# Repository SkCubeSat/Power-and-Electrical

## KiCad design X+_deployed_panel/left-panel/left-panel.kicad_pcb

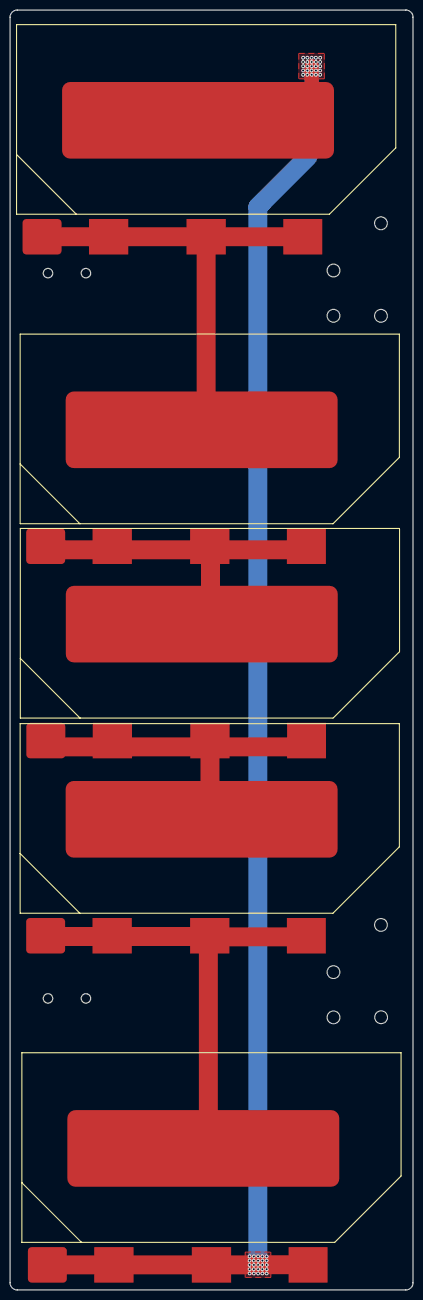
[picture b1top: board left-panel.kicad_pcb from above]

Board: 2 copper layers, 85.0 x 270.0 mm, 14 parts (1 on the bottom side), 6 nets.

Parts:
Buck1: DF13_Horizontal
H1, H4, H5, H6, H7, H8, H9, H10: MountingHole; MountingHole_2.7mm_M2.5
SC1, SC3, SC4, SC5, SC6: S8040_CIC; Solar_Cell_Lightricity_S8040_CIC

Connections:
unnamed: Buck1.1 (BCR+), SC6.2 (-)
unnamed: Buck1.2 (BCR-), SC1.1 (+)
unnamed: SC1.2 (-), SC3.1 (+)
unnamed: SC3.2 (-), SC4.1 (+)
unnamed: SC4.2 (-), SC5.1 (+)
unnamed: SC5.2 (-), SC6.1 (+)

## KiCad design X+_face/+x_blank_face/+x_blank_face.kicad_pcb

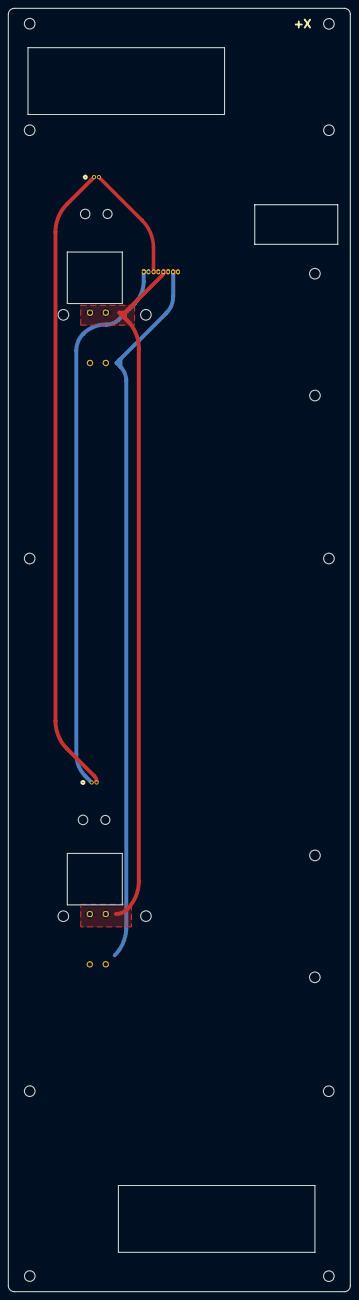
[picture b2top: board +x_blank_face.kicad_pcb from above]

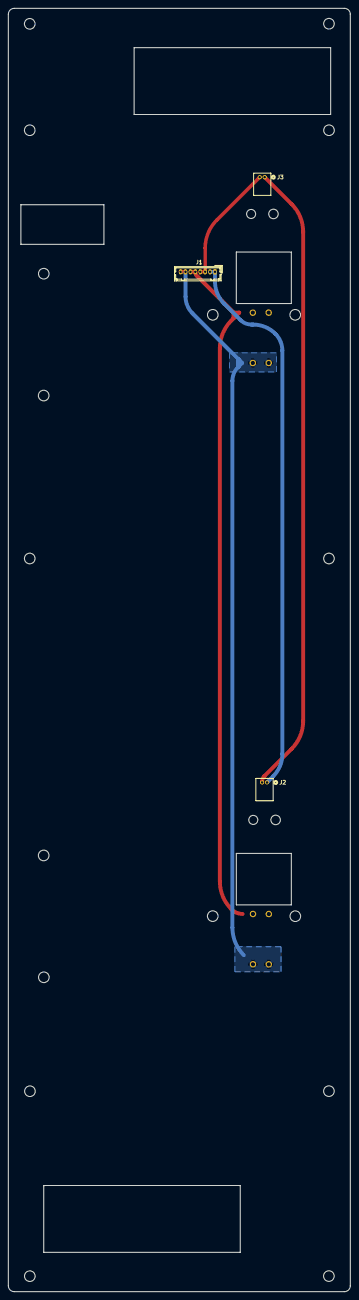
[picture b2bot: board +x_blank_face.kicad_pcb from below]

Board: 2 copper layers, 87.0 x 326.5 mm, 25 parts (3 on the bottom side), 5 nets.

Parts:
H1, H1#2, H2, H2#2, H3, H3#2, H4, H4#2, H5, H6, H7, H8, H9, H10, H11, H13, H14, H15: MountingHole; MountingHole_2.7mm_M2.5
J1: Conn_01x08_Pin; DF13-8P
J2, J3: Conn_01x02_Pin; CON2_1X2_UR_DF13
R1, R2, R3, R4: 75; UB3C-75RF1

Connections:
/12VPDM: J1.7, J1.8, R1.1, R2.1, R3.1, R4.1
/+X Drain: J1.5, J1.6, R1.2, R2.2, R3.2, R4.2
/-X Serial Out: J1.3, J1.4, J3.2
GND: J1.1, J1.2, J2.1
unnamed: J2.2, J3.1

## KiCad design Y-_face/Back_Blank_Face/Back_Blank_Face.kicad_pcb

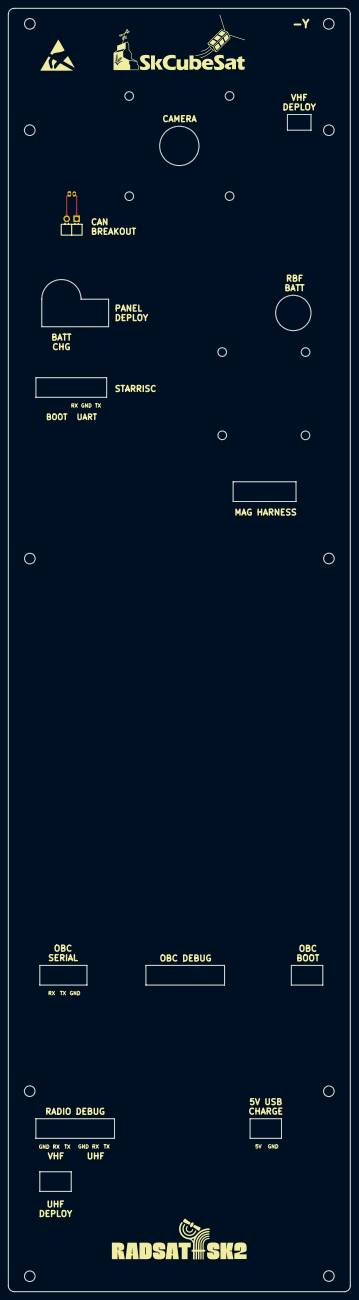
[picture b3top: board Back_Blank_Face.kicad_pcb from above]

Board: 2 copper layers, 87.0 x 326.5 mm, 20 parts (1 on the bottom side), 2 nets.

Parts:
H1, H2, H3, H4, H5, H6, H9, H10, H11, H14: MountingHole; MountingHole_2.7mm_M2.5
H15, H16, H17, H18, H19, H20, H21, H22: MountingHole; MountingHole_2.2mm_M2
J1: Conn_01x02_Pin; Hirose_DF13-02P-1.25DSA_1x02_P1.25mm_Vertical
J2: Conn_01x02_Pin; PinHeader_1x02_P2.54mm_Horizontal

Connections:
unnamed: J1.1, J2.2
unnamed: J1.2, J2.1
